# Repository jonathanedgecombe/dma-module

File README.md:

A DMA module designed for the RC2014.

### BOM
- 1x Z84C1008PEG (IC1)
- 1x 74HCT688N (IC2)
- 1x 74LS157N (IC3)
- 1x 2x40 90 degree pin header (JP1)
- 3x 1x3 90 degree pin header (JP2, JP3, JP5)
- 2x 1x2 90 degree pin header (JP4, JP6)
- 3x 100nF 2.54mm ceramic capacitors (C1, C2, C3)
- 1x 10K 8-resistor bussed network (RN1)
- 1x MCNDP-08V 8-way DIP switch (S1)

### Board photos and renders

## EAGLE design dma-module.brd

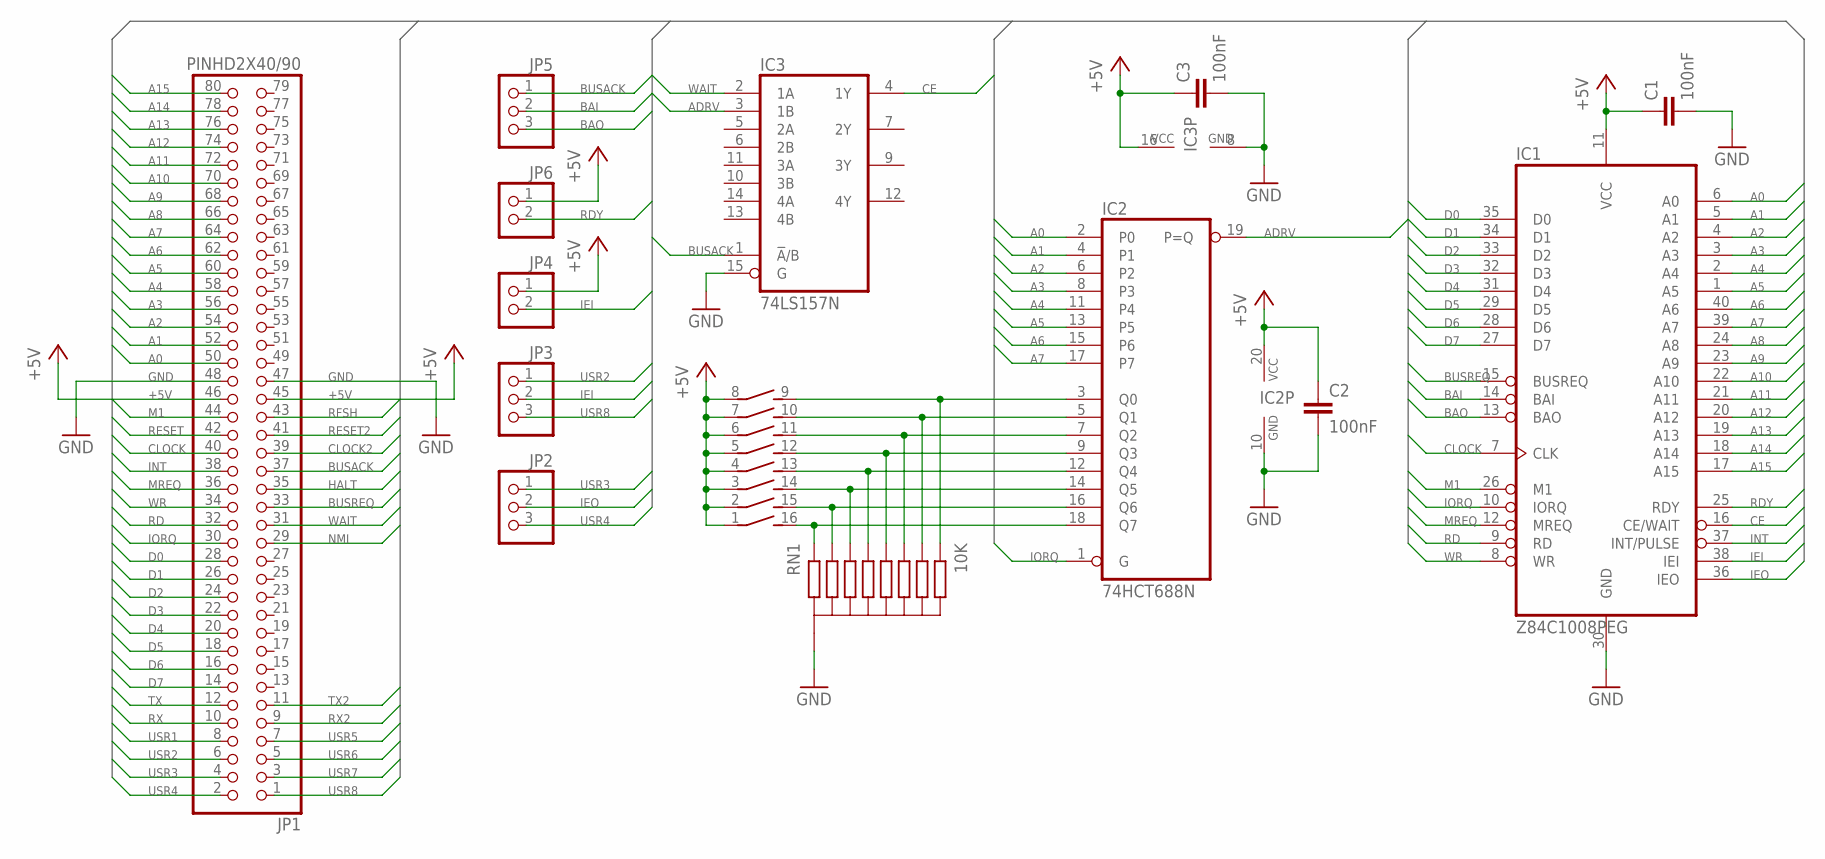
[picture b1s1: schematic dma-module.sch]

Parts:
C1, C2, C3: 100nF; C025-025X050
IC1: Z84C1008PEG; DIP40
IC2: 74HCT688N; DIL20
IC3: 74LS157N; DIL16
JP1: PINHD2X40/90; 2X40/90
JP2, JP3, JP5: PINHD-1X3/90; 1X03/90
JP4, JP6: PINHD-1X2/90; 1X02/90
RN1: 10K; RBUS
S1: DIP08SB

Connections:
+5V: C1.1, C2.1, C3.1, IC1.11 (VCC), IC2.20 (VCC), IC3.16 (VCC), JP1.45, JP1.46, JP4.1, JP6.1, S1.1, S1.2 (1), S1.3 (1), S1.4 (1), S1.5 (1), S1.6 (1), S1.7 (1), S1.8 (1)
A0: IC1.6 (A0), IC2.2 (P0), JP1.50
A1: IC1.5 (A1), IC2.4 (P1), JP1.52
A2: IC1.4 (A2), IC2.6 (P2), JP1.54
A3: IC1.3 (A3), IC2.8 (P3), JP1.56
A4: IC1.2 (A4), IC2.11 (P4), JP1.58
A5: IC1.1 (A5), IC2.13 (P5), JP1.60
A6: IC1.40 (A6), IC2.15 (P6), JP1.62
A7: IC1.39 (A7), IC2.17 (P7), JP1.64
A8: IC1.24 (A8), JP1.66
A9: IC1.23 (A9), JP1.68
A10: IC1.22 (A10), JP1.70
A11: IC1.21 (A11), JP1.72
A12: IC1.20 (A12), JP1.74
A13: IC1.19 (A13), JP1.76
A14: IC1.18 (A14), JP1.78
A15: IC1.17 (A15), JP1.80
ADRV: IC2.19 (P=Q), IC3.3 (1B)
BAI: IC1.14 (BAI), JP5.2
BAO: IC1.13 (BAO), JP5.3
BUSACK: IC3.1 (!A!/B), JP1.37, JP5.1
BUSREQ: IC1.15 (BUSREQ), JP1.33
CE: IC1.16 (CE/WAIT), IC3.4 (1Y)
CLOCK: IC1.7 (CLK), JP1.40
CLOCK2: JP1.39
D0: IC1.35 (D0), JP1.28
D1: IC1.34 (D1), JP1.26
D2: IC1.33 (D2), JP1.24
D3: IC1.32 (D3), JP1.22
D4: IC1.31 (D4), JP1.20
D5: IC1.29 (D5), JP1.18
D6: IC1.28 (D6), JP1.16
D7: IC1.27 (D7), JP1.14
GND: C1.2, C2.2, C3.2, IC1.30 (GND), IC2.10 (GND), IC3.8 (GND), IC3.15 (G), JP1.47, JP1.48, RN1.P$1 (COM)
HALT: JP1.35
IEI: IC1.38 (IEI), JP3.2, JP4.2
IEO: IC1.36 (IEO), JP2.2
INT: IC1.37 (INT/PULSE), JP1.38
IORQ: IC1.10 (IORQ), IC2.1 (G), JP1.30
M1: IC1.26 (M1), JP1.44
MREQ: IC1.12 (MREQ), JP1.36
unnamed: IC2.3 (Q0), RN1.P$9 (R8), S1.9 (2)
unnamed: IC2.5 (Q1), RN1.P$8 (R7), S1.10 (2)
unnamed: IC2.7 (Q2), RN1.P$7 (R6), S1.11 (2)
unnamed: IC2.9 (Q3), RN1.P$6 (R5), S1.12 (2)
unnamed: IC2.12 (Q4), RN1.P$5 (R4), S1.13 (2)
unnamed: IC2.14 (Q5), RN1.P$4 (R3), S1.14 (2)
unnamed: IC2.16 (Q6), RN1.P$3 (R2), S1.15 (2)
unnamed: IC2.18 (Q7), RN1.P$2 (R1), S1.16 (2)
NMI: JP1.29
RD: IC1.9 (RD), JP1.32
RDY: IC1.25 (RDY), JP6.2
RESET: JP1.42
RESET2: JP1.41
RFSH: JP1.43
RX: JP1.10
RX2: JP1.9
TX: JP1.12
TX2: JP1.11
USR1: JP1.8
USR2: JP1.6, JP3.1
USR3: JP1.4, JP2.1
USR4: JP1.2, JP2.3
USR5: JP1.7
USR6: JP1.5
USR7: JP1.3
USR8: JP1.1, JP3.3
WAIT: IC3.2 (1A), JP1.31
WR: IC1.8 (WR), JP1.34

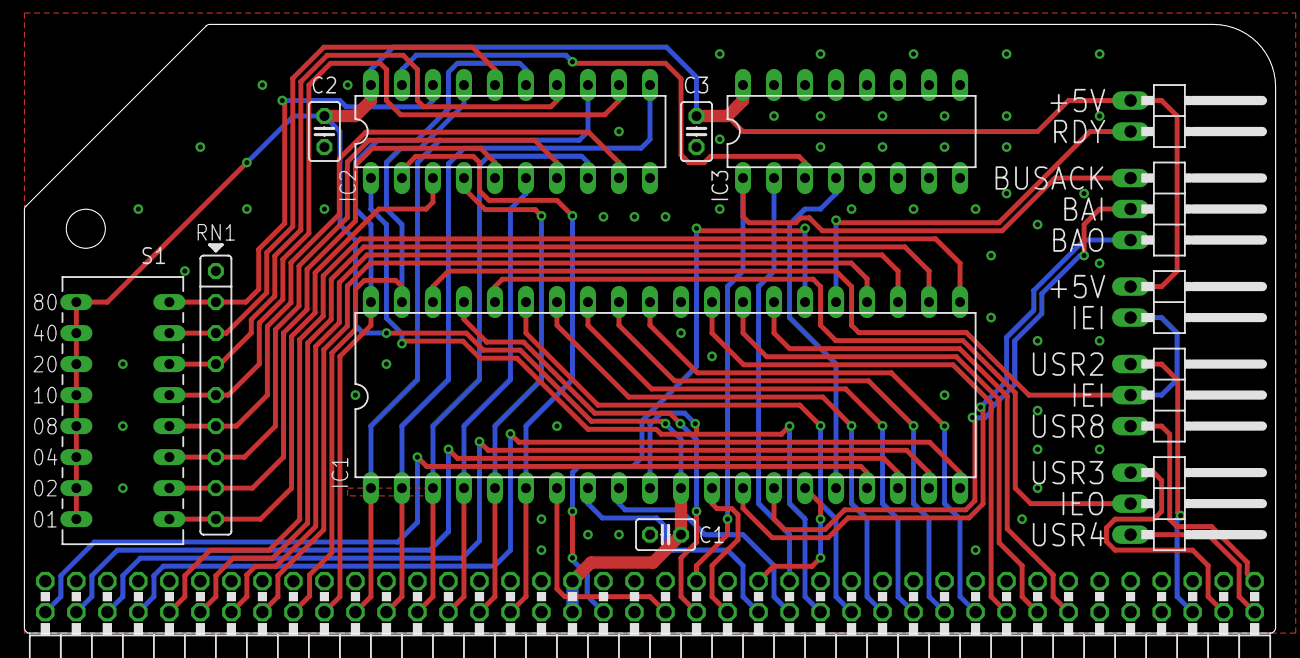
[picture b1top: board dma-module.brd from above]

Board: 2 copper layers, 102.5 x 49.9 mm, 14 parts (0 on the bottom side), 55 nets.

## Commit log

2021-02-24 Add license
2021-02-24 Add readme
2021-02-24 Add board photo
2021-02-24 Add BOM to readme
